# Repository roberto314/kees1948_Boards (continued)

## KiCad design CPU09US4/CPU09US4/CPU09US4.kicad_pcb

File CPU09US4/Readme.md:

# kees1948_Boards
kees 1948 Uniflex Serial Board Remake

This is my recreation of the Uniflex Serial Board. It is a merge of the SR4 and the US4 Board with some SMD Components. It has two pinouts for external modules. One with a RS232 Converter and a female SUB-D9 connector, and one for a USB-Serial Converter with USB-C or micro-USB Connector. The modules can be found on ebay.

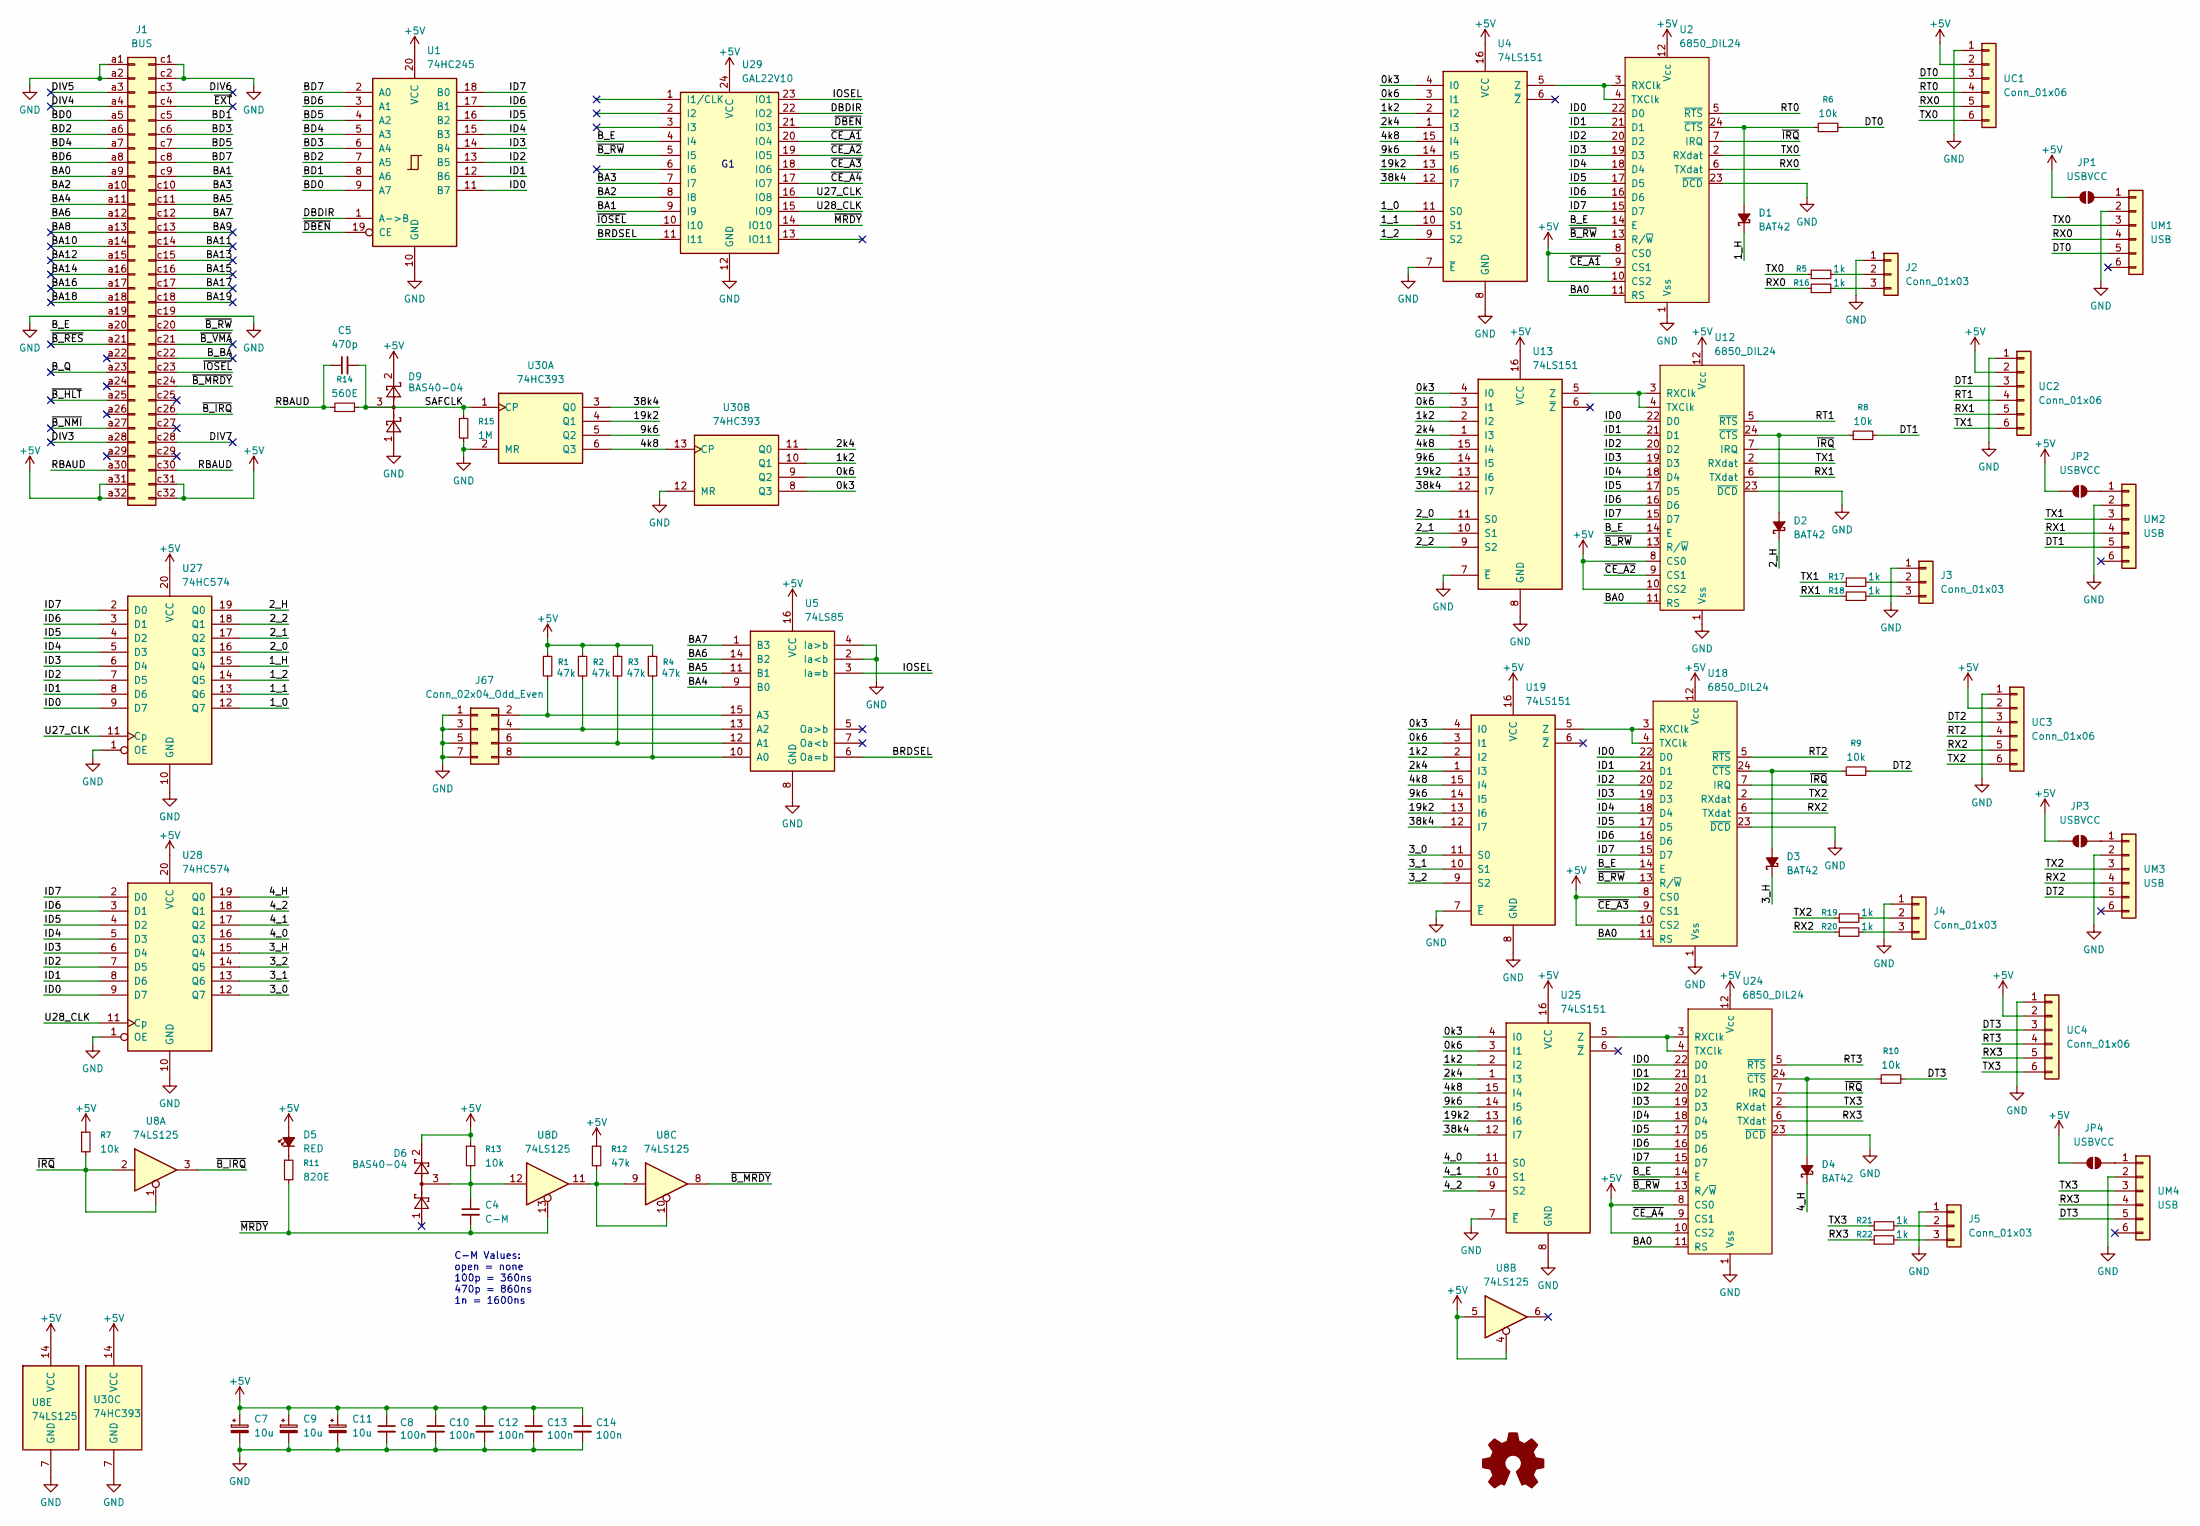
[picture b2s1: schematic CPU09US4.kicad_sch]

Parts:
C4: C-M; C_1206_3216Metric_Pad1.33x1.80mm_HandSolder
C5: 470p; C_1206_3216Metric_Pad1.33x1.80mm_HandSolder
C7, C9, C11: 10u; CP_EIA-7343-31_Kemet-D_HandSolder
C8, C10, C12, C13, C14: 100n; C_1206_3216Metric_Pad1.33x1.80mm_HandSolder
D1, D2, D3, D4: BAT42; D_DO-15_P10.16mm_Horizontal
D5: RED; LED_D5.0mm
D6, D9: BAS40-04; SOT-23
J1: BUS; DIN41612_C_2x32_Male_Horizontal_THT
J2, J3, J4, J5: Conn_01x03; PinHeader_1x03_P2.54mm_Vertical
J67: Conn_02x04_Odd_Even; PinHeader_2x04_P2.54mm_Vertical
JP1, JP2, JP3, JP4: USBVCC; SolderJumper-2_P1.3mm_Open_Pad1.0x1.5mm
R1, R2, R3, R4, R12: 47k; R_1206_3216Metric_Pad1.30x1.75mm_HandSolder
R5, R16, R17, R18, R19, R20, R21, R22: 1k; R_1206_3216Metric_Pad1.30x1.75mm_HandSolder
R6, R7, R8, R9, R10, R13: 10k; R_1206_3216Metric_Pad1.30x1.75mm_HandSolder
R11: 820E; R_1206_3216Metric_Pad1.30x1.75mm_HandSolder
R14: 560E; R_1206_3216Metric_Pad1.30x1.75mm_HandSolder
R15: 1M; R_1206_3216Metric_Pad1.30x1.75mm_HandSolder
U1: 74HC245; DIP-20_W7.62mm
U2, U12, U18, U24: 6850_DIL24; DIP-24_W15.24mm
U4, U13, U19, U25: 74LS151; DIP-16_W7.62mm
U5: 74LS85; DIP-16_W7.62mm
U8: 74LS125; DIP-14_W7.62mm
U27, U28: 74HC574; DIP-20_W7.62mm
U29: GAL22V10; DIP-24_W7.62mm
U30: 74HC393; DIP-14_W7.62mm
UC1, UC2, UC3, UC4: Conn_01x06; PinHeader_1x06_P2.54mm_Vertical
UM1, UM2, UM3, UM4: USB; PinHeader_1x06_P2.54mm_Vertical

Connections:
+5V: C7.1, C8.1, C9.1, C10.1, C11.1, C12.1, C13.1, C14.1, D5.2 (A), D6.2, D9.2, J1.a31, J1.a32, J1.c31, J1.c32, JP1.1 (A), JP2.1 (A), JP3.1 (A), JP4.1 (A), R1.1, R2.1, R3.1, R4.1, R7.1, R12.1, R13.1, U1.20 (VCC), U2.8 (CS0), U2.10 (CS2), U2.12 (Vcc), U4.16 (VCC), U5.16 (VCC), U8.4, U8.5, U8.14 (VCC), U12.8 (CS0), U12.10 (CS2), U12.12 (Vcc), U13.16 (VCC), U18.8 (CS0), U18.10 (CS2), U18.12 (Vcc), U19.16 (VCC), U24.8 (CS0), U24.10 (CS2), U24.12 (Vcc), U25.16 (VCC), U27.20 (VCC), U28.20 (VCC), U29.24 (VCC), U30.14 (VCC), UC1.2, UC2.2, UC3.2, UC4.2
/0k3: U4.4 (I0), U13.4 (I0), U19.4 (I0), U25.4 (I0), U30.8 (Q3)
/0k6: U4.3 (I1), U13.3 (I1), U19.3 (I1), U25.3 (I1), U30.9 (Q2)
/1_0: U4.11 (S0), U27.12 (Q7)
/1_1: U4.10 (S1), U27.13 (Q6)
/1_2: U4.9 (S2), U27.14 (Q5)
/1_H: D1.1 (K), U27.15 (Q4)
/1k2: U4.2 (I2), U13.2 (I2), U19.2 (I2), U25.2 (I2), U30.10 (Q1)
/2_0: U13.11 (S0), U27.16 (Q3)
/2_1: U13.10 (S1), U27.17 (Q2)
/2_2: U13.9 (S2), U27.18 (Q1)
/2_H: D2.1 (K), U27.19 (Q0)
/2k4: U4.1 (I3), U13.1 (I3), U19.1 (I3), U25.1 (I3), U30.11 (Q0)
/3_0: U19.11 (S0), U28.12 (Q7)
/3_1: U19.10 (S1), U28.13 (Q6)
/3_2: U19.9 (S2), U28.14 (Q5)
/3_H: D3.1 (K), U28.15 (Q4)
/4_0: U25.11 (S0), U28.16 (Q3)
/4_1: U25.10 (S1), U28.17 (Q2)
/4_2: U25.9 (S2), U28.18 (Q1)
/4_H: D4.1 (K), U28.19 (Q0)
/4k8: U4.15 (I4), U13.15 (I4), U19.15 (I4), U25.15 (I4), U30.6 (Q3), U30.13 (CP)
/9k6: U4.14 (I5), U13.14 (I5), U19.14 (I5), U25.14 (I5), U30.5 (Q2)
/19k2: U4.13 (I6), U13.13 (I6), U19.13 (I6), U25.13 (I6), U30.4 (Q1)
/38k4: U4.12 (I7), U13.12 (I7), U19.12 (I7), U25.12 (I7), U30.3 (Q0)
/BA0: J1.a9, U2.11 (RS), U12.11 (RS), U18.11 (RS), U24.11 (RS)
/BA1: J1.c9, U29.9 (I9)
/BA2: J1.a10, U29.8 (I8)
/BA3: J1.c10, U29.7 (I7)
/BA4: J1.a11, U5.9 (B0)
/BA5: J1.c11, U5.11 (B1)
/BA6: J1.a12, U5.14 (B2)
/BA7: J1.c12, U5.1 (B3)
/BA8: J1.a13
/BA9: J1.c13
/BA10: J1.a14
/BA11: J1.c14
/BA12: J1.a15
/BA13: J1.c15
/BA14: J1.a16
/BA15: J1.c16
/BA16: J1.a17
/BA17: J1.c17
/BA18: J1.a18
/BA19: J1.c18
/BD0: J1.a5, U1.9 (A7)
/BD1: J1.c5, U1.8 (A6)
/BD2: J1.a6, U1.7 (A5)
/BD3: J1.c6, U1.6 (A4)
/BD4: J1.a7, U1.5 (A3)
/BD5: J1.c7, U1.4 (A2)
/BD6: J1.a8, U1.3 (A1)
/BD7: J1.c8, U1.2 (A0)
/BRDSEL: U5.6 (Oa=b), U29.11 (I11)
/B_BA: J1.c22
/B_E: J1.a20, U2.14 (E), U12.14 (E), U18.14 (E), U24.14 (E), U29.4 (I4)
/B_Q: J1.a23
/DBDIR: U1.1 (A->B), U29.22 (IO2)
/DIV3: J1.a28
/DIV4: J1.a4
/DIV5: J1.a3
/DIV6: J1.c3
/DIV7: J1.c28
/DT0: R6.2, UC1.3, UM1.5
/DT1: R8.2, UC2.3, UM2.5
/DT2: R9.2, UC3.3, UM3.5
/DT3: R10.2, UC4.3, UM4.5
/ID0: U1.11 (B7), U2.22 (D0), U12.22 (D0), U18.22 (D0), U24.22 (D0), U27.9 (D7), U28.9 (D7)
/ID1: U1.12 (B6), U2.21 (D1), U12.21 (D1), U18.21 (D1), U24.21 (D1), U27.8 (D6), U28.8 (D6)
/ID2: U1.13 (B5), U2.20 (D2), U12.20 (D2), U18.20 (D2), U24.20 (D2), U27.7 (D5), U28.7 (D5)
/ID3: U1.14 (B4), U2.19 (D3), U12.19 (D3), U18.19 (D3), U24.19 (D3), U27.6 (D4), U28.6 (D4)
/ID4: U1.15 (B3), U2.18 (D4), U12.18 (D4), U18.18 (D4), U24.18 (D4), U27.5 (D3), U28.5 (D3)
/ID5: U1.16 (B2), U2.17 (D5), U12.17 (D5), U18.17 (D5), U24.17 (D5), U27.4 (D2), U28.4 (D2)
/ID6: U1.17 (B1), U2.16 (D6), U12.16 (D6), U18.16 (D6), U24.16 (D6), U27.3 (D1), U28.3 (D1)
/ID7: U1.18 (B0), U2.15 (D7), U12.15 (D7), U18.15 (D7), U24.15 (D7), U27.2 (D0), U28.2 (D0)
/IOSEL: U5.3 (Ia=b), U29.23 (IO1)
/RBAUD: C5.1, J1.a30, J1.c30, R14.1
/RT0: U2.5 (~RTS), UC1.4
/RT1: U12.5 (~RTS), UC2.4
/RT2: U18.5 (~RTS), UC3.4
/RT3: U24.5 (~RTS), UC4.4
/RX0: R16.1, U2.6 (TXdat), UC1.5, UM1.4
/RX1: R18.1, U12.6 (TXdat), UC2.5, UM2.4
/RX2: R20.1, U18.6 (TXdat), UC3.5, UM3.4
/RX3: R22.1, U24.6 (TXdat), UC4.5, UM4.4
/SAFCLK: C5.2, D9.3, R14.2, R15.1, U30.1 (CP)
/TX0: R5.1, U2.2 (RXdat), UC1.6, UM1.3
/TX1: R17.1, U12.2 (RXdat), UC2.6, UM2.3
/TX2: R19.1, U18.2 (RXdat), UC3.6, UM3.3
/TX3: R21.1, U24.2 (RXdat), UC4.6, UM4.3
/U27_CLK: U27.11 (Cp), U29.16 (IO8)
/U28_CLK: U28.11 (Cp), U29.15 (IO9)
/~B_HLT: J1.a25
/~B_IRQ: J1.c26, U8.3
/~B_MRDY: J1.c24, U8.8
/~B_NMI: J1.a27
/~B_RES: J1.a21
/~B_RW: J1.c20, U2.13 (R/~W), U12.13 (R/~W), U18.13 (R/~W), U24.13 (R/~W), U29.5 (I5)
/~B_VMA: J1.c21
/~CE_A1: U2.9 (CS1), U29.20 (IO4)
/~CE_A2: U12.9 (CS1), U29.19 (IO5)
/~CE_A3: U18.9 (CS1), U29.18 (IO6)
/~CE_A4: U24.9 (CS1), U29.17 (IO7)
/~DBEN: U1.19 (CE), U29.21 (IO3)
/~EXT: J1.c4
/~IOSEL: J1.c23, U29.10 (I10)
/~IRQ: R7.2, U2.7 (IRQ), U8.1, U8.2, U12.7 (IRQ), U18.7 (IRQ), U24.7 (IRQ)
/~MRDY: C4.2, R11.2, U8.13, U29.14 (IO10)
GND: C7.2, C8.2, C9.2, C10.2, C11.2, C12.2, C13.2, C14.2, D9.1, J1.a1, J1.a2, J1.a19, J1.c1, J1.c2, J1.c19, J2.1, J3.1, J4.1, J5.1, J67.1, J67.3, J67.5, J67.7, R15.2, U1.10 (GND), U2.1 (Vss), U2.23 (~DCD), U4.7 (~E), U4.8 (GND), U5.2 (Ia<b), U5.4 (Ia>b), U5.8 (GND), U8.7 (GND), U12.1 (Vss), U12.23 (~DCD), U13.7 (~E), U13.8 (GND), U18.1 (Vss), U18.23 (~DCD), U19.7 (~E), U19.8 (GND), U24.1 (Vss), U24.23 (~DCD), U25.7 (~E), U25.8 (GND), U27.1 (OE), U27.10 (GND), U28.1 (OE), U28.10 (GND), U29.12 (GND), U30.2 (MR), U30.7 (GND), U30.12 (MR), UC1.1, UC2.1, UC3.1, UC4.1, UM1.2, UM2.2, UM3.2, UM4.2
unnamed: C4.1, D6.3, R13.2, U8.12
unnamed: D1.2 (A), R6.1, U2.24 (~CTS)
unnamed: D2.2 (A), R8.1, U12.24 (~CTS)
unnamed: D3.2 (A), R9.1, U18.24 (~CTS)
unnamed: D4.2 (A), R10.1, U24.24 (~CTS)
unnamed: D5.1 (K), R11.1
unnamed: J2.2, R5.2
unnamed: J2.3, R16.2
unnamed: J3.2, R17.2
unnamed: J3.3, R18.2
unnamed: J4.2, R19.2
unnamed: J4.3, R20.2
unnamed: J5.2, R21.2
unnamed: J5.3, R22.2
unnamed: J67.2, R1.2, U5.15 (A3)
unnamed: J67.4, R2.2, U5.13 (A2)
unnamed: J67.6, R3.2, U5.12 (A1)
unnamed: J67.8, R4.2, U5.10 (A0)
unnamed: JP1.2 (B), UM1.1
unnamed: JP2.2 (B), UM2.1
unnamed: JP3.2 (B), UM3.1
unnamed: JP4.2 (B), UM4.1
unnamed: R12.2, U8.9, U8.10, U8.11
unnamed: U2.3 (RXClk), U2.4 (TXClk), U4.5 (Z)
unnamed: U12.3 (RXClk), U12.4 (TXClk), U13.5 (Z)
unnamed: U18.3 (RXClk), U18.4 (TXClk), U19.5 (Z)
unnamed: U24.3 (RXClk), U24.4 (TXClk), U25.5 (Z)

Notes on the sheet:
C-M Values: open = none 100p = 360ns 470p = 860ns 1n = 1600ns

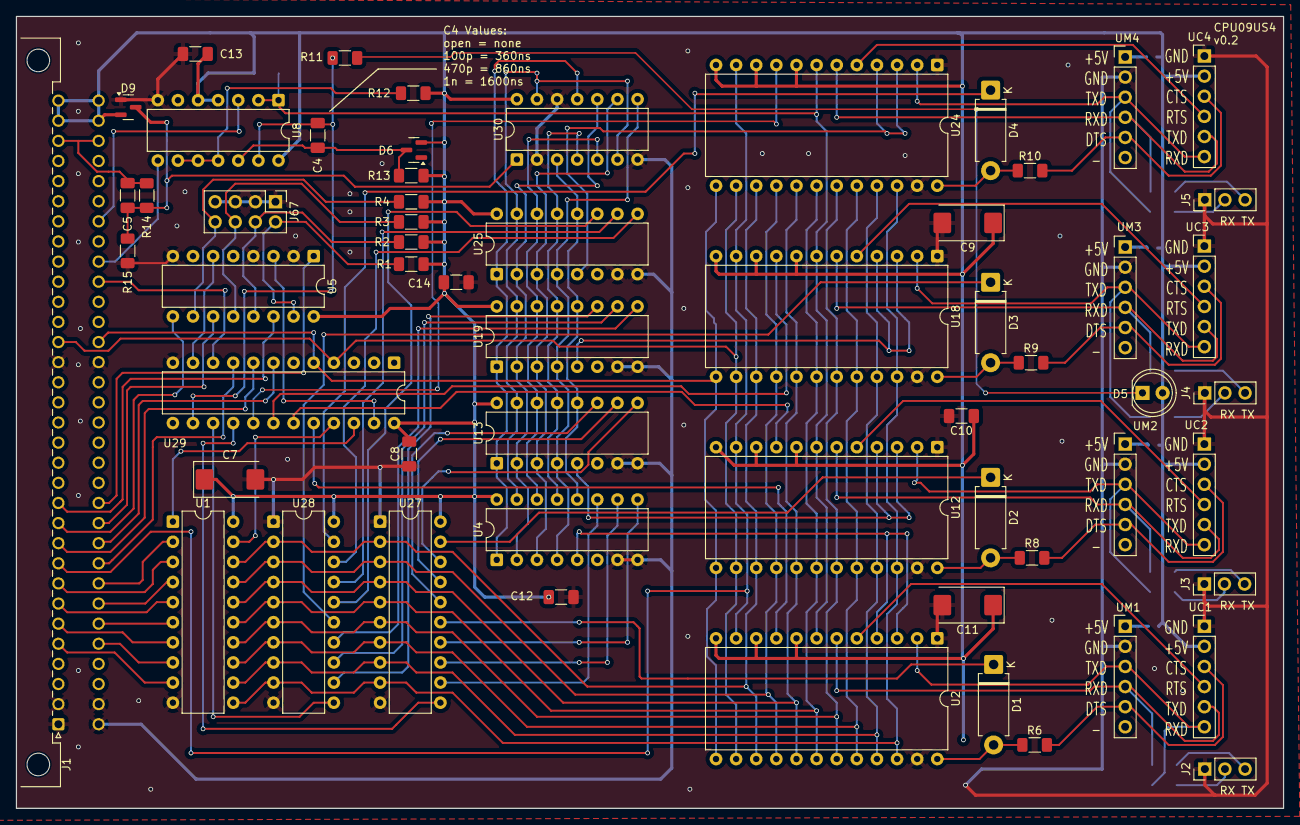
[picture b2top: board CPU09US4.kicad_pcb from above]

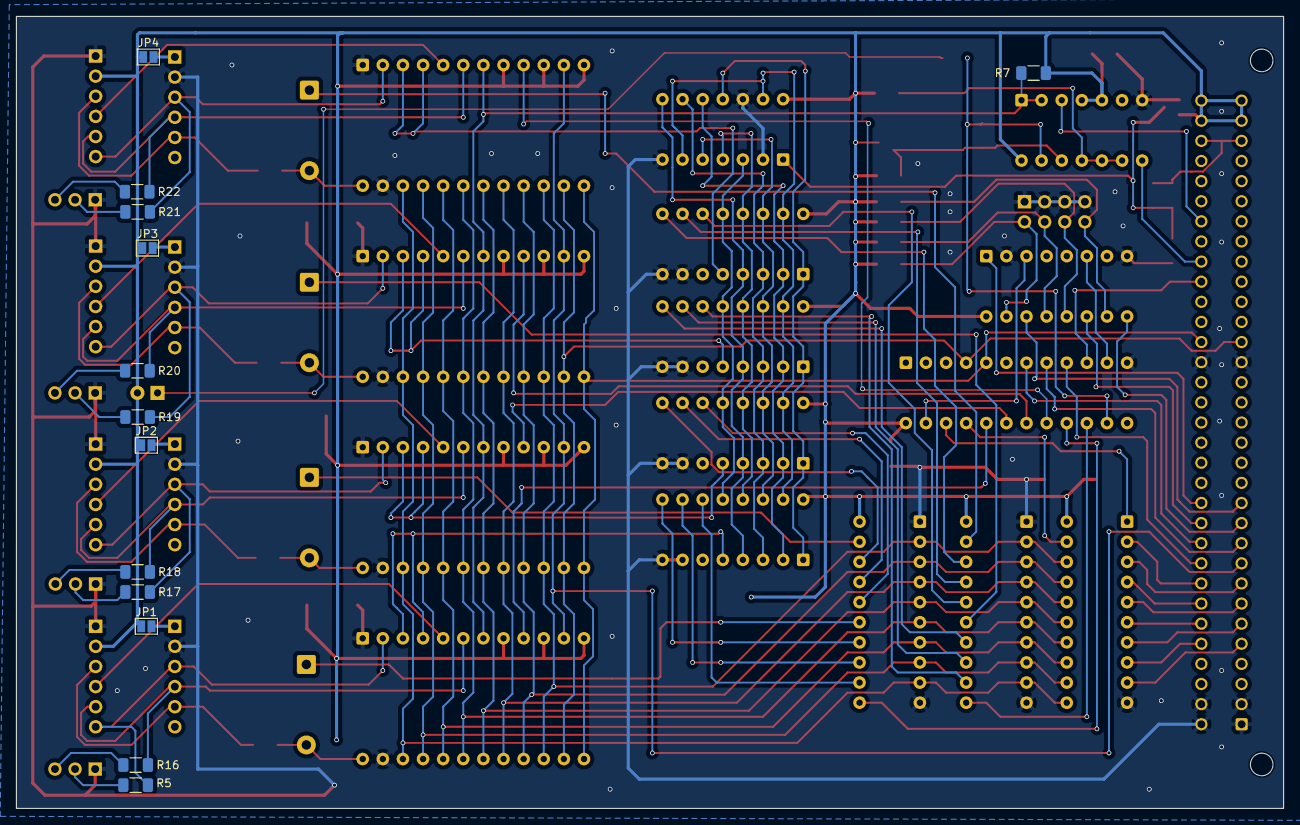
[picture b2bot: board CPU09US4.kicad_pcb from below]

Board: 2 copper layers, 160.0 x 100.0 mm, 72 parts (13 on the bottom side), 112 nets.

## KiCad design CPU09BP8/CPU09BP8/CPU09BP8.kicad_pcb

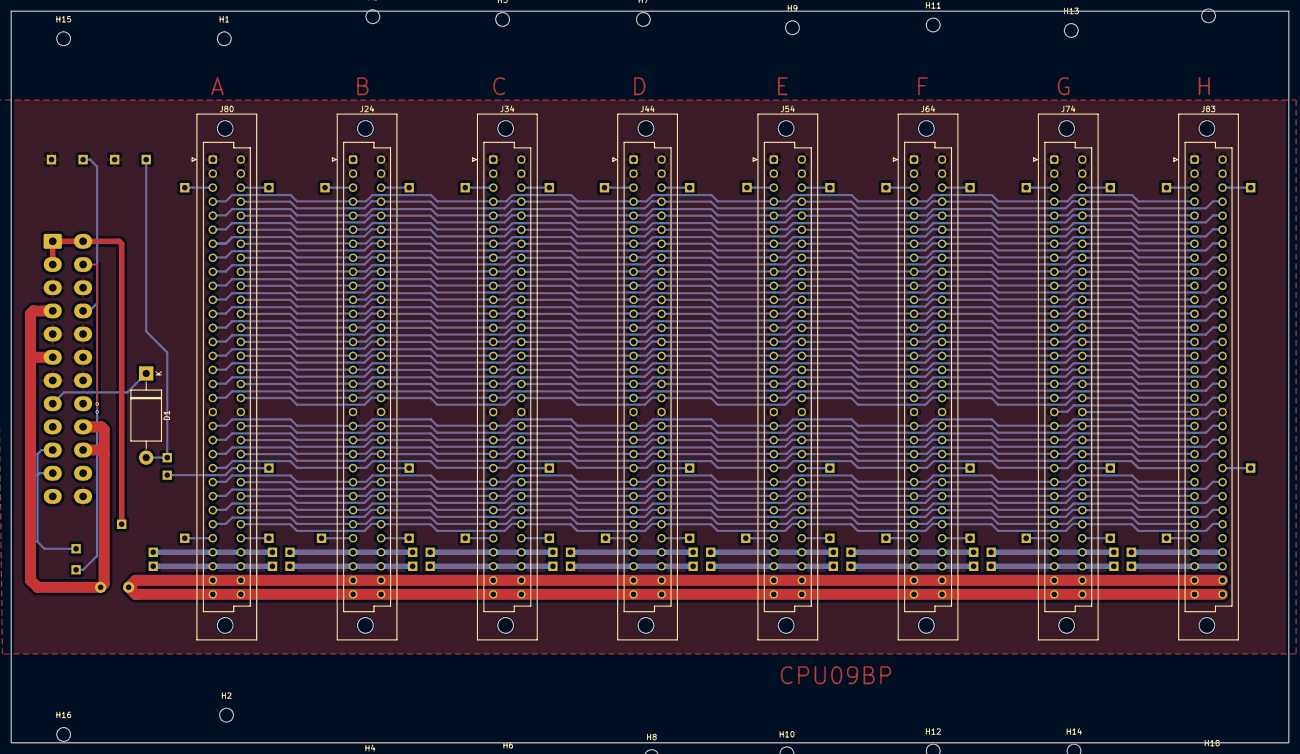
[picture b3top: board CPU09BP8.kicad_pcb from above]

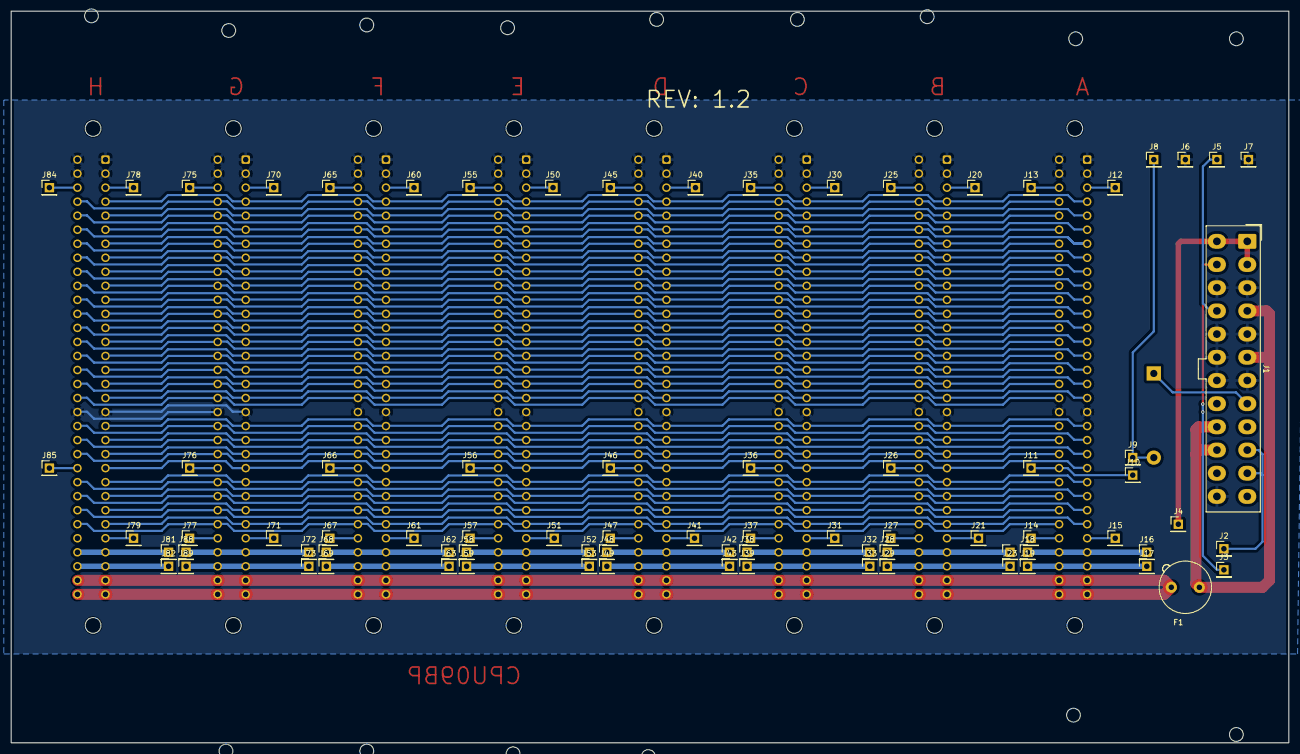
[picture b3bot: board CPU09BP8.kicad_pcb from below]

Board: 2 copper layers, 231.4 x 132.5 mm, 107 parts (80 on the bottom side), 109 nets.

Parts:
D1: D_Small_Filled; D_DO-201AE_P15.24mm_Horizontal
F1: 1A; Fuseholder_TR5_Littelfuse_No560_No460
H1, H2, H3, H4, H5, H6, H7, H8, H9, H10, H11, H12, H13, H14, H15, H16, H17, H18: M2.5; MountingHole_2.5mm
J1: ATX-24; Molex_Mini-Fit_Jr_5566-24A_2x12_P4.20mm_Vertical
J2: +12V; PinHeader_1x01_P2.54mm_Vertical
J3: -12V; PinHeader_1x01_P2.54mm_Vertical
J4: 3.3V; PinHeader_1x01_P2.54mm_Vertical
J5: PSON; PinHeader_1x01_P2.54mm_Vertical
J6, J7: GND; PinHeader_1x01_P2.54mm_Vertical
J8: ~{RES}; PinHeader_1x01_P2.54mm_Vertical
J9: ~{RES0}; PinHeader_1x01_P2.54mm_Vertical
J10: C_23; PinHeader_1x01_P2.54mm_Vertical
J11: C_23A; PinHeader_1x01_P2.54mm_Vertical
J12: C_1A; PinHeader_1x01_P2.54mm_Vertical
J13: C_2A; PinHeader_1x01_P2.54mm_Vertical
J14: C_29A; PinHeader_1x01_P2.54mm_Vertical
J15: C_28A; PinHeader_1x01_P2.54mm_Vertical
J16: ACCA; PinHeader_1x01_P2.54mm_Vertical
J17: ACCB; PinHeader_1x01_P2.54mm_Vertical
J18: A29; PinHeader_1x01_P2.54mm_Vertical
J19: A30; PinHeader_1x01_P2.54mm_Vertical
J20: C_1B; PinHeader_1x01_P2.54mm_Vertical
J21: C_28B; PinHeader_1x01_P2.54mm_Vertical
J22: BCCA; PinHeader_1x01_P2.54mm_Vertical
J23: BCCB; PinHeader_1x01_P2.54mm_Vertical
J24: BUS-B; DIN41612_C_2x32_Female_Vertical_THT
J25: C_2B; PinHeader_1x01_P2.54mm_Vertical
J26: C_23B; PinHeader_1x01_P2.54mm_Vertical
J27: C_29B; PinHeader_1x01_P2.54mm_Vertical
J28: B29; PinHeader_1x01_P2.54mm_Vertical
J29: B30; PinHeader_1x01_P2.54mm_Vertical
J30: C_1C; PinHeader_1x01_P2.54mm_Vertical
J31: C_28C; PinHeader_1x01_P2.54mm_Vertical
J32: CCCA; PinHeader_1x01_P2.54mm_Vertical
J33: CCCB; PinHeader_1x01_P2.54mm_Vertical
J34: BUS-C; DIN41612_C_2x32_Female_Vertical_THT
J35: C_2C; PinHeader_1x01_P2.54mm_Vertical
J36: C_23C; PinHeader_1x01_P2.54mm_Vertical
J37: C_29C; PinHeader_1x01_P2.54mm_Vertical
J38: C29; PinHeader_1x01_P2.54mm_Vertical
J39: C30; PinHeader_1x01_P2.54mm_Vertical
J40: C_1D; PinHeader_1x01_P2.54mm_Vertical
J41: C_28D; PinHeader_1x01_P2.54mm_Vertical
J42: DCCA; PinHeader_1x01_P2.54mm_Vertical
J43: DCCB; PinHeader_1x01_P2.54mm_Vertical
J44: BUS-D; DIN41612_C_2x32_Female_Vertical_THT
J45: C_2D; PinHeader_1x01_P2.54mm_Vertical
J46: C_23D; PinHeader_1x01_P2.54mm_Vertical
J47: C_29D; PinHeader_1x01_P2.54mm_Vertical
J48: D29; PinHeader_1x01_P2.54mm_Vertical
J49: D30; PinHeader_1x01_P2.54mm_Vertical
J50: C_1E; PinHeader_1x01_P2.54mm_Vertical
J51: C_28E; PinHeader_1x01_P2.54mm_Vertical
J52: ECCA; PinHeader_1x01_P2.54mm_Vertical
J53: ECCB; PinHeader_1x01_P2.54mm_Vertical
J54: BUS-E; DIN41612_C_2x32_Female_Vertical_THT
J55: C_2E; PinHeader_1x01_P2.54mm_Vertical
J56: C_23E; PinHeader_1x01_P2.54mm_Vertical
J57: C_29E; PinHeader_1x01_P2.54mm_Vertical
J58: E29; PinHeader_1x01_P2.54mm_Vertical
J59: E30; PinHeader_1x01_P2.54mm_Vertical
J60: C_1F; PinHeader_1x01_P2.54mm_Vertical
J61: C_28F; PinHeader_1x01_P2.54mm_Vertical
J62: FCCA; PinHeader_1x01_P2.54mm_Vertical
J63: FCCB; PinHeader_1x01_P2.54mm_Vertical
J64: BUS-F; DIN41612_C_2x32_Female_Vertical_THT
J65: C_2F; PinHeader_1x01_P2.54mm_Vertical
J66: C_23F; PinHeader_1x01_P2.54mm_Vertical
J67: C_29F; PinHeader_1x01_P2.54mm_Vertical
J68, J88: F29; PinHeader_1x01_P2.54mm_Vertical
J69, J89: F30; PinHeader_1x01_P2.54mm_Vertical
J70: C_1G; PinHeader_1x01_P2.54mm_Vertical
J71: C_28G; PinHeader_1x01_P2.54mm_Vertical
J72, J81: GCCA; PinHeader_1x01_P2.54mm_Vertical
J73, J82: GCCB; PinHeader_1x01_P2.54mm_Vertical
J74: BUS-G; DIN41612_C_2x32_Female_Vertical_THT
J75: C_2G; PinHeader_1x01_P2.54mm_Vertical
J76: C_23G; PinHeader_1x01_P2.54mm_Vertical
J77: C_29G; PinHeader_1x01_P2.54mm_Vertical
J78: C_1H; PinHeader_1x01_P2.54mm_Vertical
J79: C_28H; PinHeader_1x01_P2.54mm_Vertical
J80: BUS-A; DIN41612_C_2x32_Female_Vertical_THT
J83: BUS-H; DIN41612_C_2x32_Female_Vertical_THT
J84: C_2H; PinHeader_1x01_P2.54mm_Vertical
J85: C_23H; PinHeader_1x01_P2.54mm_Vertical

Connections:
+5V: F1.2, J24.a31, J24.a32, J24.c31, J24.c32, J34.a31, J34.a32, J34.c31, J34.c32, J44.a31, J44.a32, J44.c31, J44.c32, J54.a31, J54.a32, J54.c31, J54.c32, J64.a31, J64.a32, J64.c31, J64.c32, J74.a31, J74.a32, J74.c31, J74.c32, J80.a31, J80.a32, J80.c31, J80.c32, J83.a31, J83.a32, J83.c31, J83.c32
/BA0: J24.a9, J34.a9, J44.a9, J54.a9, J64.a9, J74.a9, J80.a9, J83.a9
/BA1: J24.c9, J34.c9, J44.c9, J54.c9, J64.c9, J74.c9, J80.c9, J83.c9
/BA2: J24.a10, J34.a10, J44.a10, J54.a10, J64.a10, J74.a10, J80.a10, J83.a10
/BA3: J24.c10, J34.c10, J44.c10, J54.c10, J64.c10, J74.c10, J80.c10, J83.c10
/BA4: J24.a11, J34.a11, J44.a11, J54.a11, J64.a11, J74.a11, J80.a11, J83.a11
/BA5: J24.c11, J34.c11, J44.c11, J54.c11, J64.c11, J74.c11, J80.c11, J83.c11
/BA6: J24.a12, J34.a12, J44.a12, J54.a12, J64.a12, J74.a12, J80.a12, J83.a12
/BA7: J24.c12, J34.c12, J44.c12, J54.c12, J64.c12, J74.c12, J80.c12, J83.c12
/BA8: J24.a13, J34.a13, J44.a13, J54.a13, J64.a13, J74.a13, J80.a13, J83.a13
/BA9: J24.c13, J34.c13, J44.c13, J54.c13, J64.c13, J74.c13, J80.c13, J83.c13
/BA10: J24.a14, J34.a14, J44.a14, J54.a14, J64.a14, J74.a14, J80.a14, J83.a14
/BA11: J24.c14, J34.c14, J44.c14, J54.c14, J64.c14, J74.c14, J80.c14, J83.c14
/BA12: J24.a15, J34.a15, J44.a15, J54.a15, J64.a15, J74.a15, J80.a15, J83.a15
/BA13: J24.c15, J34.c15, J44.c15, J54.c15, J64.c15, J74.c15, J80.c15, J83.c15
/BA14: J24.a16, J34.a16, J44.a16, J54.a16, J64.a16, J74.a16, J80.a16, J83.a16
/BA15: J24.c16, J34.c16, J44.c16, J54.c16, J64.c16, J74.c16, J80.c16, J83.c16
/BA16: J24.a17, J34.a17, J44.a17, J54.a17, J64.a17, J74.a17, J80.a17, J83.a17
/BA17: J24.c17, J34.c17, J44.c17, J54.c17, J64.c17, J74.c17, J80.c17, J83.c17
/BA18: J24.a18, J34.a18, J44.a18, J54.a18, J64.a18, J74.a18, J80.a18, J83.a18
/BA19: J24.c18, J34.c18, J44.c18, J54.c18, J64.c18, J74.c18, J80.c18, J83.c18
/BD0: J24.a5, J34.a5, J44.a5, J54.a5, J64.a5, J74.a5, J80.a5, J83.a5
/BD1: J24.c5, J34.c5, J44.c5, J54.c5, J64.c5, J74.c5, J80.c5, J83.c5
/BD2: J24.a6, J34.a6, J44.a6, J54.a6, J64.a6, J74.a6, J80.a6, J83.a6
/BD3: J24.c6, J34.c6, J44.c6, J54.c6, J64.c6, J74.c6, J80.c6, J83.c6
/BD4: J24.a7, J34.a7, J44.a7, J54.a7, J64.a7, J74.a7, J80.a7, J83.a7
/BD5: J24.c7, J34.c7, J44.c7, J54.c7, J64.c7, J74.c7, J80.c7, J83.c7
/BD6: J24.a8, J34.a8, J44.a8, J54.a8, J64.a8, J74.a8, J80.a8, J83.a8
/BD7: J24.c8, J34.c8, J44.c8, J54.c8, J64.c8, J74.c8, J80.c8, J83.c8
/B_BA: J24.c22, J34.c22, J44.c22, J54.c22, J64.c22, J74.c22, J80.c22, J83.c22
/B_E: J24.a20, J34.a20, J44.a20, J54.a20, J64.a20, J74.a20, J80.a20, J83.a20
/B_MR: J24.c24, J34.c24, J44.c24, J54.c24, J64.c24, J74.c24, J80.c24, J83.c24
/B_Q: J24.a23, J34.a23, J44.a23, J54.a23, J64.a23, J74.a23, J80.a23, J83.a23
/DIV3: J15.1, J80.a28
/DIV4: J24.a4, J34.a4, J44.a4, J54.a4, J64.a4, J74.a4, J80.a4, J83.a4
/DIV5: J12.1, J80.a3
/DIV6: J13.1, J80.c3
/DIV7: J14.1, J80.c28
/RBAUD: J17.1, J19.1, J80.a30, J80.c30
/a22: J24.a22, J34.a22, J44.a22, J54.a22, J64.a22, J74.a22, J80.a22, J83.a22
/a24: J24.a24, J34.a24, J44.a24, J54.a24, J64.a24, J74.a24, J80.a24, J83.a24
/a26: J24.a26, J34.a26, J44.a26, J54.a26, J64.a26, J74.a26, J80.a26, J83.a26
/c25: J24.c25, J34.c25, J44.c25, J54.c25, J64.c25, J74.c25, J80.c25, J83.c25
/c27: J24.c27, J34.c27, J44.c27, J54.c27, J64.c27, J74.c27, J80.c27, J83.c27
/~B_HLT: J24.a25, J34.a25, J44.a25, J54.a25, J64.a25, J74.a25, J80.a25, J83.a25
/~B_IRQ: J24.c26, J34.c26, J44.c26, J54.c26, J64.c26, J74.c26, J80.c26, J83.c26
/~B_NMI: J24.a27, J34.a27, J44.a27, J54.a27, J64.a27, J74.a27, J80.a27, J83.a27
/~B_RES: J24.a21, J34.a21, J44.a21, J54.a21, J64.a21, J74.a21, J80.a21, J83.a21
/~B_RW: J24.c20, J34.c20, J44.c20, J54.c20, J64.c20, J74.c20, J80.c20, J83.c20
/~B_VMA: J24.c21, J34.c21, J44.c21, J54.c21, J64.c21, J74.c21, J80.c21, J83.c21
/~EXT: J24.c4, J34.c4, J44.c4, J54.c4, J64.c4, J74.c4, J80.c4, J83.c4
/~RES: J10.1, J11.1, J80.c23
GND: J1.3 (GND), J1.5 (GND), J1.7 (GND), J1.15 (GND), J1.17 (GND), J1.18 (GND), J1.19 (GND), J1.24 (GND), J6.1, J7.1, J24.a1, J24.a2, J24.a19, J24.c1, J24.c2, J24.c19, J34.a1, J34.a2, J34.a19, J34.c1, J34.c2, J34.c19, J44.a1, J44.a2, J44.a19, J44.c1, J44.c2, J44.c19, J54.a1, J54.a2, J54.a19, J54.c1, J54.c2, J54.c19, J64.a1, J64.a2, J64.a19, J64.c1, J64.c2, J64.c19, J74.a1, J74.a2, J74.a19, J74.c1, J74.c2, J74.c19, J80.a1, J80.a2, J80.a19, J80.c1, J80.c2, J80.c19, J83.a1, J83.a2, J83.a19, J83.c1, J83.c2, J83.c19
unnamed: D1.2 (A), J8.1, J9.1
unnamed: D1.1 (K), J1.8 (PWR_OK)
unnamed: F1.1, J1.4 (+5V), J1.6 (+5V), J1.21 (+5V), J1.22 (+5V), J1.23 (+5V)
unnamed: J1.14 (-12V), J3.1
unnamed: J1.16 (PS_ON#), J5.1
unnamed: J1.10 (+12V), J1.11 (+12V), J2.1
unnamed: J1.1 (+3.3V), J1.2 (+3.3V), J1.12 (+3.3V), J1.13 (+3.3V), J4.1
unnamed: J16.1, J18.1, J80.a29, J80.c29
unnamed: J20.1, J24.a3
unnamed: J21.1, J24.a28
unnamed: J22.1, J24.a29, J24.c29, J28.1
unnamed: J23.1, J24.a30, J24.c30, J29.1
unnamed: J24.c3, J25.1
unnamed: J24.c23, J26.1
unnamed: J24.c28, J27.1
unnamed: J30.1, J34.a3
unnamed: J31.1, J34.a28
unnamed: J32.1, J34.a29, J34.c29, J38.1
unnamed: J33.1, J34.a30, J34.c30, J39.1
unnamed: J34.c3, J35.1
unnamed: J34.c23, J36.1
unnamed: J34.c28, J37.1
unnamed: J40.1, J44.a3
unnamed: J41.1, J44.a28
unnamed: J42.1, J44.a29, J44.c29, J48.1
unnamed: J43.1, J44.a30, J44.c30, J49.1
unnamed: J44.c3, J45.1
unnamed: J44.c23, J46.1
unnamed: J44.c28, J47.1
unnamed: J50.1, J54.a3
unnamed: J51.1, J54.a28
unnamed: J52.1, J54.a29, J54.c29, J58.1
unnamed: J53.1, J54.a30, J54.c30, J59.1
unnamed: J54.c3, J55.1
unnamed: J54.c23, J56.1
unnamed: J54.c28, J57.1
unnamed: J60.1, J64.a3
unnamed: J61.1, J64.a28
unnamed: J62.1, J64.a29, J64.c29, J68.1
unnamed: J63.1, J64.a30, J64.c30, J69.1
unnamed: J64.c3, J65.1
unnamed: J64.c23, J66.1
unnamed: J64.c28, J67.1
unnamed: J70.1, J74.a3
unnamed: J71.1, J74.a28
unnamed: J72.1, J74.a29, J74.c29, J88.1
unnamed: J73.1, J74.a30, J74.c30, J89.1
unnamed: J74.c3, J75.1
unnamed: J74.c23, J76.1
unnamed: J74.c28, J77.1
unnamed: J78.1, J83.a3
unnamed: J79.1, J83.a28
unnamed: J81.1, J83.a29, J83.c29
unnamed: J82.1, J83.a30, J83.c30
unnamed: J83.c3, J84.1
unnamed: J83.c23, J85.1
